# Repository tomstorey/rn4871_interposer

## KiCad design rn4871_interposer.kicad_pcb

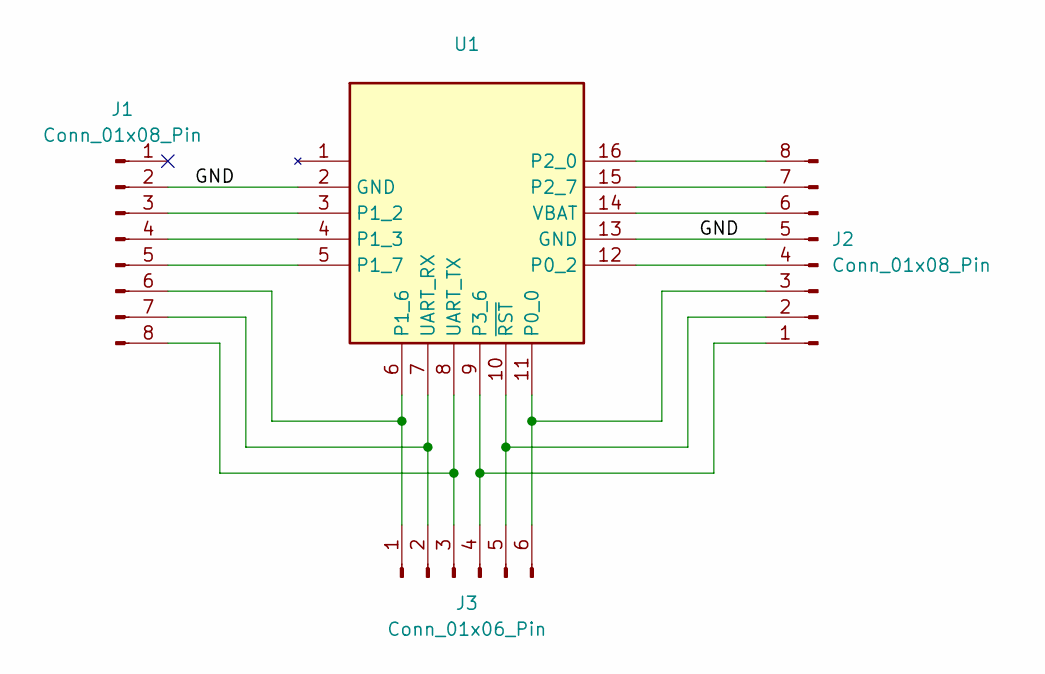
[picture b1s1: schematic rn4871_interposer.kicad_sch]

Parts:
J1, J2: Conn_01x08_Pin; PinHeader_1x08_P2.54mm_Vertical
J3: Conn_01x06_Pin; PinHeader_1x06_P2.54mm_Vertical
U1: RN4871

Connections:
/GND: J1.2, J2.5, U1.2 (GND), U1.13 (GND)
unnamed: J1.3, U1.3 (P1_2)
unnamed: J1.4, U1.4 (P1_3)
unnamed: J1.5, U1.5 (P1_7)
unnamed: J1.6, J3.1, U1.6 (P1_6)
unnamed: J1.7, J3.2, U1.7 (UART_RX)
unnamed: J1.8, J3.3, U1.8 (UART_TX)
unnamed: J2.1, J3.4, U1.9 (P3_6)
unnamed: J2.2, J3.5, U1.10 (~RST)
unnamed: J2.3, J3.6, U1.11 (P0_0)
unnamed: J2.4, U1.12 (P0_2)
unnamed: J2.6, U1.14 (VBAT)
unnamed: J2.7, U1.15 (P2_7)
unnamed: J2.8, U1.16 (P2_0)

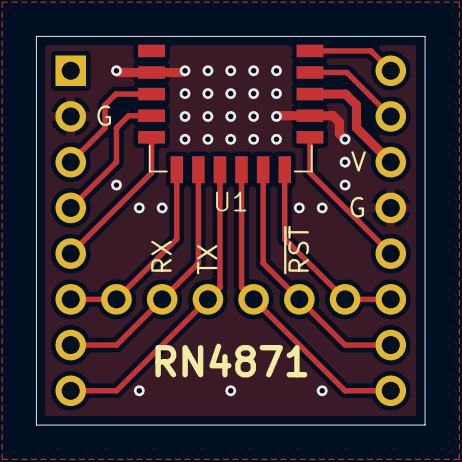
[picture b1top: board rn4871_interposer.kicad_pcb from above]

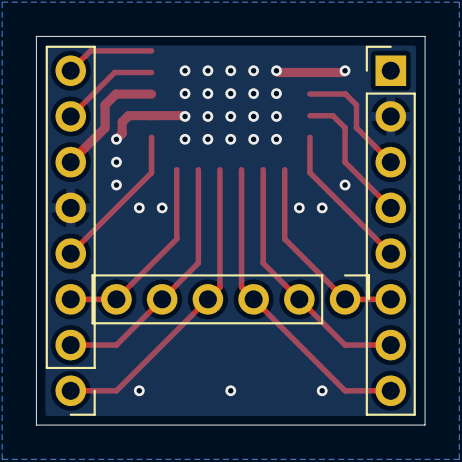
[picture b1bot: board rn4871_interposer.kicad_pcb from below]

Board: 2 copper layers, 21.6 x 21.6 mm, 4 parts (3 on the bottom side), 14 nets.

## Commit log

2024-08-03 First release
